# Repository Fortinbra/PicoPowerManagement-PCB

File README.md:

# PicoPowerManagement-PCB
A PCB for using an RP2350 to manage the power in a Mini-Rack

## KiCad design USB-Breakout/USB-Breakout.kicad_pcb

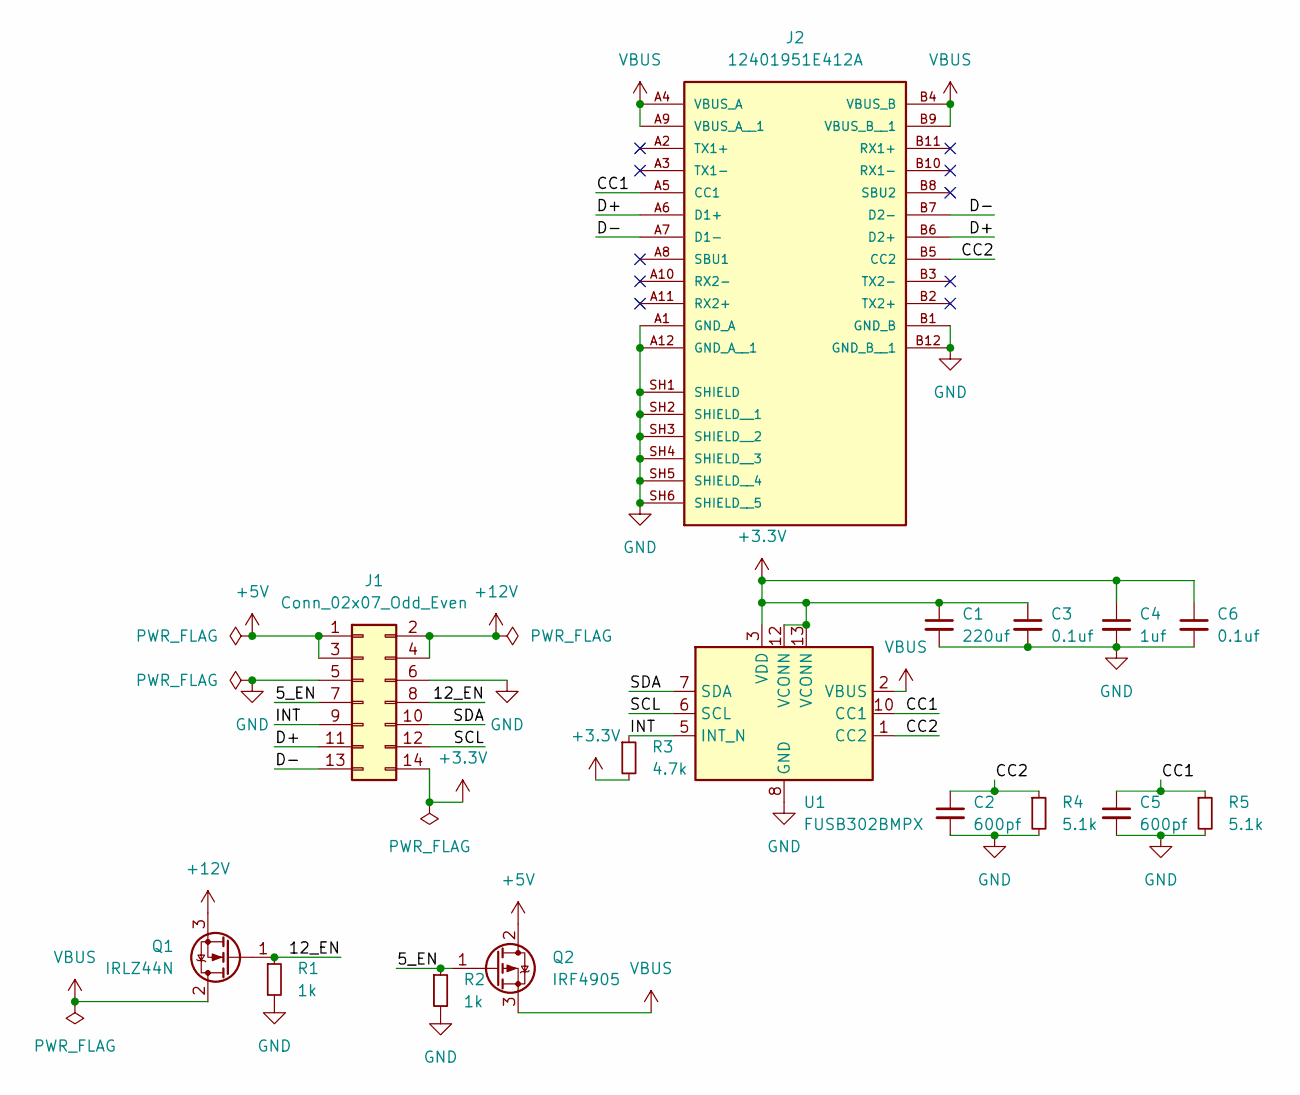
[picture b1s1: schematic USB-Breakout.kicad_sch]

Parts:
C1: 220uf; C_1206_3216Metric_Pad1.33x1.80mm_HandSolder
C2, C5: 600pf; C_Rect_L9.0mm_W6.4mm_P7.50mm_MKT
C3, C6: 0.1uf; C_0402_1005Metric_Pad0.74x0.62mm_HandSolder
C4: 1uf; C_0201_0603Metric_Pad0.64x0.40mm_HandSolder
J1: Conn_02x07_Odd_Even; PinHeader_2x07_P2.54mm_Vertical
J2: 12401951E412A; AMPHENOL_12401951E412A; PARTREV 9
Q1: IRLZ44N; TO-220-3_Vertical
Q2: IRF4905; TO-220-3_Vertical
R1, R2: 1k; R_0603_1608Metric_Pad0.98x0.95mm_HandSolder
R3: 4.7k; R_0603_1608Metric_Pad0.98x0.95mm_HandSolder
R4, R5: 5.1k; R_0603_1608Metric_Pad0.98x0.95mm_HandSolder
U1: FUSB302BMPX; WQFN-14-1EP_2.5x2.5mm_P0.5mm_EP1.45x1.45mm

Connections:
+3.3V: C1.1, C3.1, C4.1, C6.1, J1.14, R3.2, U1.3 (VDD), U1.4 (VDD), U1.12 (VCONN), U1.13 (VCONN)
+5V: J1.1, J1.3, Q2.2 (D)
+12V: J1.2, J1.4, Q1.3 (S)
/5_EN: J1.7, Q2.1 (G), R2.1
/12_EN: J1.8, Q1.1 (G), R1.1
/CC1: C5.1, J2.A5 (CC1), R5.1, U1.10 (CC1), U1.11 (CC1)
/CC2: C2.1, J2.B5 (CC2), R4.1, U1.1 (CC2), U1.14 (CC2)
/D+: J1.11, J2.A6 (D1+), J2.B6 (D2+)
/D-: J1.13, J2.A7 (D1-), J2.B7 (D2-)
/INT: J1.9, R3.1, U1.5 (INT_N)
/SCL: J1.12, U1.6 (SCL)
/SDA: J1.10, U1.7 (SDA)
GND: C1.2, C2.2, C3.2, C4.2, C5.2, C6.2, J1.5, J1.6, J2.A1 (GND_A), J2.A12 (GND_A__1), J2.B1 (GND_B), J2.B12 (GND_B__1), J2.SH1 (SHIELD), J2.SH2 (SHIELD__1), J2.SH3 (SHIELD__2), J2.SH4 (SHIELD__3), J2.SH5 (SHIELD__4), J2.SH6 (SHIELD__5), R1.2, R2.2, R4.2, R5.2, U1.8 (GND), U1.9 (GND), U1.15 (GND)
VBUS: J2.A4 (VBUS_A), J2.A9 (VBUS_A__1), J2.B4 (VBUS_B), J2.B9 (VBUS_B__1), Q1.2 (D), Q2.3 (S), U1.2 (VBUS)

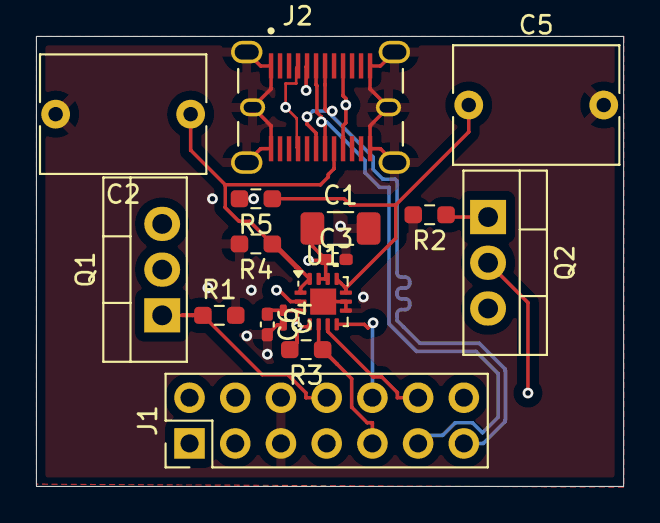
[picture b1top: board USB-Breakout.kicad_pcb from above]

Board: 4 copper layers, 32.6 x 25.0 mm, 16 parts (0 on the bottom side), 14 nets.

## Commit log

2025-03-13 Add KiCad project files and update .gitignore for Visual Studio and KiCad
2025-03-13 Add USB-C library files and license documentation for KiCad
2025-03-14 Update documentation and improve project structure for better usability
2025-03-24 confused now
